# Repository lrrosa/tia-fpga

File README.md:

# tia-fpga

An FPGA replacement for the **Television Interface Adaptor (TIA)** — the custom
`C010444` / `C010444D` (NTSC) video and sound chip of the Atari 2600.

Revision **B** is the digital interface board between a Sipeed Tang Nano 9K
module and the TIA's DIP-40 socket, for use with a real 6507 (on a breadboard or
in an actual 2600). Revision A, the first study, was never built.

| Front | Back |
|:---:|:---:|
|  |  |
| Tang Nano sockets face **up**; the logic sits in the channel between the rows | The TIA's DIP-40 pins face **down** into the socket, over the ground pour |

61.6 × 34.54 mm, two layers. Every row lands on the 2.54 mm grid — the
DIP-40's 15.24 mm and the Tang Nano's 22.86 mm — and the board is a little
shorter than the module it carries, as it has to be: in a real 2600 the TIA,
the 6507 and the RIOT sit millimetres apart.

---

## Why this exists

The TIA has **6,193 transistors** — 1,657 of which are NMOS pull-ups, leaving
about 4,500 of actual logic. It fits in any modern FPGA with room to spare:
synthesising a known implementation yields **311 flip-flops** and roughly 2,200
basic gates.

Size was never the problem. Two other things are:

1. **The analogue boundary.** The chroma generator is an analogue delay line
   trimmed by an external 500 kΩ potentiometer (pin 10, `DEL`). It has no direct
   digital equivalent.
2. **5 volts.** No FPGA with enough capacity is 5 V tolerant. And the TIA
   generates the 6507's Φ0 clock, which requires
   V<sub>IH</sub> = V<sub>cc</sub> − 0.2 V ≈ **4.8 V** — not a TTL level. A 3.3 V
   output will not clock the 6507 reliably, and the failure mode is nasty: it
   works intermittently, or works cold and quits once warm.

This revision solves (2) and leaves (1) for later.

## What is on the board

| Ref | Part | Function |
|-----|------|----------|
| J1, J4 | 1x24 sockets | Sipeed Tang Nano 9K module (GW1NR-LV9QN88PC6/I5): J1 takes its **J6** row, J4 its **J5** |
| J2, J3 | 1x20 SIP strips | Plug into the DIP-40 socket in place of the C010444 |
| D1 | MBR0540 | Feeds the module's 5 V pin from the socket, and blocks its USB from feeding the console |
| **U1** | **74AHCT125** | **Φ0 and RDY buffer, powered from +5 V.** The critical part |
| U2 | 74LVC245A | D0–D7 bidirectional bus. A side = FPGA, B side = TIA |
| U3 | 74LVC541A | A0–A5 and R/W into the FPGA; Φ2 buffered to a spare pad |
| U4 | 74LVC541A | /CS0, /CS3, triggers I4/I5 and the 3.579545 MHz crystal clock |
| U5 | 74LVC1G32 | `/CS0 OR /CS3`: `/OE` for the 245, and the FPGA's chip select |
| U6–U9 | 74LVC2G07 | Open-drain drivers for SYNC, LUM0–2, COL, BLK, AUD0 and AUD1 |

The video and sound pads — SYNC, LUM0–2, COL, BLK, AUD0 and AUD1 — each go
through one channel of U6–U9. On the die every one of them is a pull-down
transistor and nothing more; the buffers make the board's pins the same, open
drain and 5 V tolerant, so the console's own pull-ups set every level. See
*Pads and levels* below.

Pin 10 (`DEL`) is marked no-connect: it is the colour trim pot, which has no
function in a replacement.

Neither of the 245's control lines comes from the FPGA. The A side faces the
FPGA, so `DIR` can be driven straight from the buffered R/W (`DIR`=1, a read,
sends FPGA → TIA), and `/OE` comes from U5. That is deliberate — see the pin
budget below.

## The pin budget, and why it constrains everything

The Tang Nano 9K's headers are 2×24, but **only 29 of those 48 pins are usable
3.3 V GPIO**:

| | Count | |
|---|---|---|
| J5 pins 1–22 | 22 | banks 1/2 at 3.3 V — all usable |
| J6 pins 1, 10, 11, 19–22 | 7 | 3.3 V — usable |
| J6 pins 2–9 | 8 | **BANK3 at 1.8 V — not usable at 3.3 V** |
| J5 23–24, J6 12–17 | 8 | HDMI differential pairs — not GPIO |
| J6 18, 23, 24 | 3 | +5V (fed through D1), GND, +3V3 |

Verified against both revisions of the official Sipeed board schematic (3672 and
3674), which agree exactly. Many of the 29 are shared with onboard peripherals
(SD card, RGB LCD, SPI LCD); they are free to reuse as long as you do not fit
those.

**Rev B uses all 29 with nothing spare.** A fully featured TIA needs about 36.
`BLK` has its pin because the FPGA reads `/CS0 OR /CS3` from U5, which makes it
for the 245 anyway, instead of taking the two selects separately.

**Chroma is fitted.** `F_COL` took the pin that used to carry Φ2, and that trade
is deliberate rather than grudging: the FPGA generates Φ0 itself, so it knows
where it is in the bus cycle and can time accesses off its own clock instead of
the 6507's output. It costs a little timing fidelity and buys back colour on the
composite and RF path — which is the difference between a board that only works
with an HDMI monitor and one that revives a console with a dead TIA while
keeping its original video. Φ2 is still buffered by U3, brought out to an
unconnected pad for a future revision.

What still does not fit: the four paddle inputs plus their dump/compare control.

Two ways to get the remaining pins back:

1. **Recover J6/2–9** (8 pins) with a local 1.8 V LDO and a fourth buffer powered
   at 1.8 V. LVC parts run down to 1.65 V and their inputs stay 5 V tolerant, so
   this works — it just adds a rail. This is the cheapest way to the paddles.
2. **Drop the module and put a bare FPGA on the board.** A part in a TQFP-100
   gives ~78 I/O against the module's 29, which ends the pin shortage outright,
   removes U5, brings Φ2 back and makes the paddles possible — and collapses a
   ~20 mm tall stack into a 1 mm chip, which matters if this has to live inside
   a closed console. It costs fine-pitch soldering and your own configuration
   and power plumbing. See `docs/bare-fpga.md`.

This is the single most important thing to know before ordering parts: the Tang
Nano 9K is big enough in *logic* by a wide margin, and tight in *pins*. Every
compromise in this design traces back to that.

## The board

Rev B is a 2-layer, **61.6 × 34.54 mm** board — shorter than the Tang Nano it
carries. In a real 2600 the TIA, the 6507 and the RIOT sit millimetres apart,
ringed by resistor networks and the cartridge slot, so the board cannot spread
sideways. The two sets of rows face opposite ways:

| y (mm) | Row | Side | Faces |
|---|---|---|---|
| 5.84 | J1 — Tang Nano **J6** | F.Cu | socket, **up** |
| 9.65 | J2 — TIA pins 1–20 | **B.Cu** | pins, **down** into the socket |
| 24.89 | J3 — TIA pins 21–40 | **B.Cu** | pins, **down** |
| 28.70 | J4 — Tang Nano **J5** | F.Cu | socket, **up** |

Both pitches land on the 2.54 mm grid: the DIP-40 rows 15.24 mm apart, the Tang
Nano's 22.86 mm, and the DIP pair centred between the sockets — 3.81 mm of gap
on each side. Which socket takes which module row is not free — see
[Which row is which](#which-row-is-which). SMD logic sits on the front in the
15.24 mm channel between the DIP rows. The open-drain drivers and their
capacitors sit in the top margin, right above the TIA pins they drive, with D1
beside them, and the channel's decoupling in the bottom margin.

| | |
|---|---|
| Size | 61.6 × 34.54 mm, 2 layers |
| Components | 24 — SOIC/SOT-23 logic, 0805 capacitors, one diode, through-hole connectors |
| Routing | 534 segments, 39 vias, 1.48 m of copper |
| Ground | B.Cu pour, 759 mm² in two islands, tied together by track |
| Track / clearance | 0.18 mm / 0.13 mm |
| **DRC** | **0 violations, 0 unconnected pads** |

### Pin assignment is solved, not listed

Which signal sits on which header position is free — any GPIO can carry any
signal — so it is chosen to put each FPGA pin as close as it can be to the pad
its net really reaches: the buffer or gate between it and the TIA socket, not
the socket pin beyond it. Solved as an assignment problem (Hungarian, over the
29 usable positions, Manhattan distance to those pads), the whole set comes to
571 mm. `F_OSC` is held to J6/1, the right PLL's own input, which costs 25.6 mm
of that and keeps the colour clock off the FPGA's general routing.

The sum is what the module's own geometry allows: J5 carries 22 of the 29
signals and sits on the row *away* from the TIA's pins 1–20, so most of the bus
crosses the channel whatever the assignment does. Solving it still beats the
alternative — the same signals laid out by hand come to 685 mm.

Rev A measured the distance to the TIA pin itself, which left out the detour
through the buffers: its data and chip-select lines crossed the board twice.
The buffers stay ordered left to right by the centroid of what they carry,
**U1, U4, U3, U2**, and against rev A the board saves copper while gaining five
parts:

| | rev A | rev B |
|---|---|---|
| Segments | 601 | **534** |
| Vias | 31 | **39** |
| Copper | 1.68 m | **1.48 m** |

`fpga/tia_fpga.cst` carries the result. Do not reshuffle those `IO_LOC` lines
casually — the layout depends on them.

Autorouted with [Freerouting](https://github.com/freerouting/freerouting) 2.2.4:
all 120 nets in about 12 s but three ground connections. Two are closed with a
via dropped on the branch's own track where it passes over the pour, and the
last two capacitors are tied to their neighbours along the free lane that runs
just inside the top edge. The channel leaves only ~1.1 mm between the header pads and the SOIC
pads, so the geometry decides whether it routes at all: it takes 0.13 mm
clearance and 0.18 mm track. The ground pour is added **after** routing —
Freerouting reads a pour as an obstacle and goes effectively single-layer if one
is present.

Files: `tia-fpga.kicad_pcb`, renders in `docs/`, fabrication output in `gerbers/`.

### Ordering a board

The files in `gerbers/` are ready for any PCB house as they are — Gerber X2
plus Excellon drill, with `FABRICATION-NOTES.txt` alongside them; zip them with
the files at the root of the archive. Nothing in it needs more than standard
low-cost capability:

| | |
|---|---|
| Size / layers | 61.6 × 34.54 mm, 2 layers, 1.6 mm FR4 |
| Min track / clearance | 0.18 mm / 0.13 mm |
| Drills | 0.30 mm (vias), 1.00 mm (connectors) |

`docs/bom-production.csv` is the parts list with suggested orderable numbers.
Three assembly points that are easy to get wrong:

- **J2/J3 mount on the BACK, pins facing DOWN**, and want **round machined
  pins** — square header pins damage a DIP socket.
- **U5–U9, C7–C10 and D1 carry their designators on the back silkscreen**,
  right behind each part: the top margin has no room for them on the front.
- **The module goes in component side up, USB-C end to the left** — see below.
- **The back silkscreen carries the licence notice** — `CERN-OHL-S v2`,
  `LRRosa 2026` and `github.com/lrrosa/tia-fpga`, between the two rows of TIA
  pins. The licence asks for it to travel with the board; keep it on a respin.
- **Pin 1 of the TIA is at the half-moon end.** The back carries that half moon,
  keyed like the chip's own package, and the numbers 1, 20, 21 and 40 beside the
  corner pads; the front repeats 1 and 40.

### Which row is which

The Tang Nano's two rows are **22.86 mm** apart (9 × 2.54), from Sipeed's own
dimension drawing, `Tang_Nano_9K_3672_size`. Pin 1 of both rows is at the USB-C
end, 2.55 mm from that edge; the HDMI connector is at the other end and
overhangs this board by about 7.5 mm, with a millimetre of module sticking out
at the USB end as well. Both hang in free air, 20 mm above the console.

Looking down at the module with the USB-C end on the left, **J6 is the upper
row and J5 the lower one**, so J1 takes J6 and J4 takes J5. Three things say so
and agree: the pin numbers silkscreened on the module's underside, the QN88's
own pin order on the top-side photo in Sipeed's datasheet, and third-party
carrier boards for the module. On your own board, look for **63** beside pin 1
of one row and **38** beside pin 1 of the other: 63 is J6/1, which this board
wires to `F_OSC`.

Rev A and the first cut of rev B had both of these wrong — 20.32 mm, and the
rows the other way round. Nothing was ever fabricated from them.

The DIP-40 row spacing (15.24 mm) is fixed by the package and is not a guess.

**The board needs tall pins.** It overhangs the neighbouring 6507 and RIOT, which
sit proud of the 2600's PCB in their own sockets. Standard DIP header pins would
put this board straight into them; a socket extender or long machined pins are
required. Measure the vertical clearance in your console — the Tang Nano's HDMI
connector adds roughly 5 mm on top.

**There are no mounting holes.** The board is held by its own pins in the TIA
socket, and there is nothing to screw into inside a 2600. Adding holes only
forced the board larger, so they were dropped.

### Known limitations

- The four paddle inputs still do not fit — see the pin budget above.
- No ground pour on F.Cu; only B.Cu is poured.

### Pads and levels

Reading the die's netlist for the RTL settled something the schematic had
assumed. **Every video and sound pad on the TIA — SYNC, LUM0–2, COL, AUD0,
AUD1, and BLK and RDY too — is a pull-down transistor and nothing else.** None
of them can drive high. Φ0 is the only output with a real driver on both
sides.

The console schematics show the other half:

| | 2600A, rev 16 | 2600 (the original board) |
|---|---|---|
| LUM0–2, SYNC | R218–R221, 3.3–4.7 kΩ to +5 V, straight into the summing resistors (R214–R217: 27, 47, 110, 24 kΩ) | R218–R221, 3.3 kΩ to +5 V, into a CD4050 run from a divider off +5 V (R231, R232: about 3.6 V), then the summing resistors (R222–R224, R234: 12, 24, 47, 10 kΩ) |
| COL | R228, 1 kΩ to +5 V; C210, 47 pF, to a second 1 kΩ pull-up (R211); 6.8 kΩ and 22 pF into the sum | R212, 1 kΩ to +5 V; C212, 47 pF, to a second 1 kΩ pull-up (R214); 22 pF and 6.8 kΩ into the sum |
| BLK | R234, 820 Ω, into the COL node (revs 14 and 15: not connected) | R213, 680 Ω, into the COL node |
| AUD0, AUD1 | joined; R206, 1 kΩ to +5 V; 0.1 µF and 18 kΩ into the sound oscillator | joined; R208, 1 kΩ to +5 V; the same coupling |

PAL consoles use a different TIA (C011903): one sound pad, AUD on pin 13 with
its own 1 kΩ pull-up, while pins 12 and 8 carry the PAL signals. This board is
for the NTSC chip.

Rev B follows the die:

- **Open drain, 5 V tolerant.** Each of those pads goes through one channel of
  a 74LVC2G07 (U6–U9) powered at 3.3 V. The FPGA drives the channel's input:
  0 pulls the socket pin low, 1 lets it go, and the console's pull-up takes the
  line wherever it took the TIA's — 5 V on a 2600A's luma lines, the CD4050's
  input on an original 2600, the colour and sound nodes through their 1 kΩ.
  Nothing on the socket side reaches the FPGA's pins.
- **BLK is driven.** It pulls low through the whole blanking interval. On the
  original 2600 (through 680 Ω) and the 2600A from rev 16 (820 Ω) it drags the
  colour node down with it: against the 1 kΩ pull-up that node only reaches
  about 2 V while blanking, so the burst — the only colour sent then — gets
  well under half the swing of the picture's colour, and a TV sets its colour
  gain by the burst. On revs 14 and 15 of the 2600A the pin is not connected,
  and nothing changes.
- **The two sound pins are joined** by a trace on an unmodified 2600, which
  open drain makes harmless either way. By default `tia_board.v` still puts
  the same pulse-width mix of both channels on both pins; for a console
  modified for stereo, `AUDIO_STEREO = 1` gives each pin its own channel, in
  non-overlapping halves of the pulse frame so the two still add correctly
  wherever they meet.
- **No video network on the board.** Rev A carried a copy of the console's
  resistor network, for use outside a console. With open-drain pads it would
  have needed all of it — pull-ups, summing resistors, the colour coupling and
  BLK's resistor — so rev B leaves it off. To take video from the socket pins
  on a breadboard, build the 2600A rev 16 column of the table above.

## Two ways to use this

**Reviving a dead console.** Pull the failed TIA, drop this in its socket, and
keep the 2600's own RF modulator or composite mod. Chroma, luma, sync and audio
come out on the same socket pins the original chip used, open drain as the
chip's are, so the console's video path is untouched.

**As a development target.** Plug it into a breadboard next to a real 6507.
The Tang Nano's HDMI connector would cost no header pins — its pins are
dedicated differential pairs on the module — but the RTL has no TMDS encoder
yet, so for now the picture comes from the socket pins, through a network like
the console's.

## The RTL

`rtl/` holds the core: horizontal counter, playfield, two players, two
missiles, ball, collisions, HMOVE, audio and the bus interface, in eleven files
of plain Verilog-2005, plus `tia_board.v`, which puts it on this board. `sim/`
holds the test harness the section below argues for, and it is not
aspirational: the core is checked against
[Sim2600](https://github.com/gregjames/Sim2600) half clock by half clock, on a
real game and on test cartridges written to hit each feature from every phase
that matters.

```bash
python sim/run.py
```

Against Donkey Kong from power-on to its first picture, and against every test
cartridge -- playfield, players, missiles, ball, collisions, HMOVE with Cosmic
Ark, resets at every phase of HBLANK, vertical delay and both sound cartridges
-- the core matches the die on every pin at every half clock.
[`sim/README.md`](sim/README.md) has the table. (The Donkey Kong traces are regenerated locally rather
than committed, since they carry the game's artwork.)

**Sim2600 wires one clock wrong, and both wirings are now in the suite.**
Upstream Sim2600 feeds the TIA's Φ2 input from the 6507's Φ1 output, the
inverse of what the console does. The die only looks at that pin through
write strobes, so everything still worked, but every write landed on the other
half of the colour clock from where a real console puts it. With the console's
wiring (`sim/patches/sim2600-phi2.patch`, traces in `sim/traces/phi2/`), five
of the core's timing rules turned out to have been fitted to the wrong side
and were re-read from the netlist — RSYNC's restart, RDY's release, how
long a reset holds an object's clock, the size gate of stretched players and
when HMOVE's comparators see a new value. The last mismatch was a mechanism
no rule had covered: HMOVE pulses in the visible line merge into the object
clocks and show on the pads half a colour clock early. The core now matches
both sets on every pin of every trace.

**The board.** `rtl/tia_board.v` is everything between the core and the board's
pins: the core's clock from a PLL locked to the console's crystal, Φ2 rebuilt
from the Φ0 the board makes itself, the data bus, chroma as that clock shifted
in phase by hue, and sound as pulse width. `fpga/tia_fpga_top.v` adds the Gowin
PLL, bus buffers and chroma ODDR. `sim/tb_board.v` replays the console-wired
traces into the board logic and checks every pin it drives, and
`fpga/build_gowin.tcl` builds the bitstream with Gowin EDA — from a directory
whose path has no spaces, since Gowin's place and route will not run in one
that does.

Getting there turned up a good deal the published documentation does not say,
all of it now in the source: which edge of the colour clock each latch runs on;
that Φ0 is a 50 per cent square wave reloaded by the horizontal counter; what
RSYNC actually does, which Towers left as "requires more investigation"; that
HMOVE's first compare must come before its first decrement, or an HMxx of -8
moves an object sixteen pixels the wrong way; that HMOVE's pulses past HBLANK
merge into the object clocks instead of counting; and exactly when a mid-line playfield
write reaches the screen. Once the harness could record the die's internal
wires as well as its pins, the netlist itself settled the rest: how a RESxx
strobe really resets an object -- by holding its clock, not by zeroing its
counter -- and how the sound counters are clocked, down to the discovery that
the two audio channels are not wired alike.

**Clocking.** The real chip is clocked by the 3.58 MHz colour clock and uses
both its edges. This core takes a faster system clock and treats the colour
clock as a signal to oversample, so everything is one clock domain, one edge,
no gated clocks. On this board `clk0` comes from the console's own crystal
through U4 and the system clock from a PLL, so the core stays locked to the
machine it is plugged into.

## Status

- [x] Rev B schematic — passes KiCad 10 ERC with 0 violations
- [x] FPGA pin assignment (`fpga/tia_fpga.cst`)
- [x] PCB layout — rev B routed, ground pour, DRC clean (0 violations, 0
      unconnected pads)
- [x] Open-drain video and sound pads and `BLK` on pin 6 — U6–U9, with
      `sim/tb_board.v` checking `BLK` against the die
- [x] Sim2600 test harness — traces, replay testbench, test cartridges
- [x] TIA RTL — matches the die on a real game and on every test cartridge
- [x] Audio -- read off the die's netlist; both channels match on every trace
- [x] Object resets, scan clock, widths and HMOVE timing -- read off the netlist
- [x] Board wrapper — `rtl/tia_board.v` and `fpga/tia_fpga_top.v`: PLL off the
      console's crystal, Φ2 rebuilt from Φ0, data bus tri-state, chroma through
      an ODDR, sound as pulse width. Checked pin by pin against the traces by
      `sim/tb_board.v`
- [x] Traces with the console's wiring of Φ2 — Sim2600 feeds the TIA the
      6507's Φ1; `sim/patches/sim2600-phi2.patch` fixes that and
      `sim/traces/phi2/` holds the re-recorded set
- [x] Synthesis check: Yosys `synth_gowin` with no warnings — the core is
      514 flip-flops and 740 LUTs, the whole board top 622 and 705, under
      10 per cent of the GW1NR-9 (`fpga/check_synth.py`)
- [x] Gowin EDA build (V1.9.11.03 Education): bitstream, no setup or hold
      violations at the slow corner, 60.4 MHz Fmax against the 57.27 MHz
      clock (`fpga/build_gowin.tcl`)
- [x] Stretched players reset mid-copy, Cosmic Ark and HMOVE pulses in the
      visible line, with the console's wiring — every trace matches
- [ ] Paddle circuit (still needs pins, see above)
- [x] Composite video path wired — the chroma pin is fitted and `tia_board.v`
      synthesises the 15 subcarrier phases, as the colour clock shifted in
      phase by hue through an ODDR (`HUE_TURN`). Never yet seen on a television
- [x] Tang Nano interface checked against Sipeed's own dimension drawing: rows
      22.86 mm apart, J6 on J1, and the module fed from the socket through D1
- [x] Boot time — the bitstream loads at 31.25 MHz (`-loading_rate 250/8` in
      `fpga/build_gowin.tcl`), about 8 ms, against the 17–58 ms the console
      takes to release the 6507's reset. Still to be measured on hardware

## Opening the project

Requires **KiCad 10**. Only stock libraries are used — there are no custom
symbols or footprints to install.

```bash
kicad tia-fpga.kicad_pro
```

To run ERC from the command line:

```bash
kicad-cli sch erc tia-fpga.kicad_sch -o erc.rpt --severity-error --severity-warning
```

## Suggested order of work

1. ~~**Build the test harness first.**~~ Done -- `sim/`. Comparing half clock
   by half clock against [Sim2600](https://github.com/gregjames/Sim2600) -- not
   an emulator, but the netlist extracted from the die shot, simulated
   transistor by transistor -- earned its keep at once. Most of what it caught
   were things the documentation states plainly enough that they looked
   settled, and none of them would have been findable by looking at a picture.
2. ~~**Rewrite the TIA one block at a time**~~ -- done, in dependency order:
   horizontal sync counter, playfield, players, missiles and ball, collisions,
   HMOVE. HMOVE really is the most treacherous; leave it last.
3. ~~**Widen the coverage.**~~ Done: the test cartridges in `sim/roms/` cover
   every CTRLPF, NUSIZ, HMOVE and AUDC value, and resets at every phase of
   HBLANK, and the core matches the die on all of them.
4. ~~**Board wrapper and synthesis**~~ -- done: `rtl/tia_board.v`,
   `fpga/tia_fpga_top.v`, `fpga/tia_fpga.sdc`, `fpga/build_gowin.tcl`.
5. **Run it on the Tang Nano alone** before touching real hardware, to separate
   bugs in the TIA from bugs in your bench wiring. Nothing here does that yet:
   the module would need the rest of the console beside the core -- a 6502, the
   RIOT and a cartridge image -- or a player that replays the recorded bus
   writes in `sim/traces/`, and either way a TMDS encoder and line doubling to
   put the picture on HDMI.
6. **This board** -- TIA-only, with a real 6507.
7. Paddles.
8. Composite colour: the phases are generated; what is left is a television to
   check the hues and the burst level against.

## Timing quirks that matter

Almost every one of these is a bug in the original chip that games came to rely
on. They are what separates "runs Combat" from "runs Pitfall II":

- **Almost none of the TIA's counters are binary.** They are polynomial
  counters (LFSRs) with wired-AND decode matrices — the horizontal sync
  counter, all five object position counters, and the audio generators. Binary
  counters with comparators will run games but get the edge effects wrong. The
  exception is each sound channel's frequency divider: a binary counter
  *compared* with AUDF, not loaded from it, so lowering AUDF below the count
  makes it run on to 31 before the channel ticks again.
- **HMOVE comb.** Strobing `HMOVE` delays the end of HBlank (the LRHB line),
  producing the 8-pixel black bar at the left edge. Pitfall II depends on it.
- **Cosmic Ark starfield.** Writing HMxx during the HMOVE window makes the
  comparator see a still-running counter. The resulting pattern *differs between
  TIA revisions*.
- **RESPn latency.** A reset strobe does not zero the counter. It holds the
  object's two-phase clock in H@1 and sets a latch, and the counter clears on
  the next H@2. A copy that was already decoded therefore survives the reset,
  and inside HBlank, where the object clock is stopped, the clear waits for
  the first colour clocks of the visible line.
- There are at least **12 NTSC TIA revisions** with observable differences.
  Decide which one you are cloning before you start.

## References

- [TIA Hardware Notes](https://www.atarihq.com/danb/files/TIA_HW_Notes.txt) — Andrew Towers, 2003. Polynomial counters, HCount tables, HMOVE timing. Does not cover audio or colour generation.
- [TIA internal schematics](https://www.atariage.com/2600/archives/schematics_tia/index.html) — 5 sheets scanned by Mark De Smet. Sheet 1: sync counter, playfield and motion registers. Sheet 2: collision register. Sheet 3: object/missile motion counters. Sheet 4: audio circuits. Sheet 5: ball motion counter.
- [10444D die shots](http://www.visual6502.org/images/pages/Atari_10444D_TIA.html) — visual6502
- [TIA Technical Manual](https://archive.org/stream/Atari_2600_TIA_Technical_Manual/Atari_2600_TIA_Technical_Manual_djvu.txt)
- [Atari 2600 Specs](https://problemkaputt.de/2k6specs.htm) — Nocash; the cleanest register map there is
- [Tang Nano 9K documentation](https://dl.sipeed.com/shareURL/TANG/Nano%209K/) — Sipeed

---

## Licence

Copyright 2026 Leonardo Roman da Rosa

```
SPDX-License-Identifier: CERN-OHL-S-2.0
```

This source describes Open Hardware and is licensed under the CERN-OHL-S v2.

You may redistribute and modify this source and make products using it under
the terms of the CERN-OHL-S v2 (https://ohwr.org/cern_ohl_s_v2.txt).

This source is distributed WITHOUT ANY EXPRESS OR IMPLIED WARRANTY, INCLUDING OF
MERCHANTABILITY, SATISFACTORY QUALITY AND FITNESS FOR A PARTICULAR PURPOSE.
Please see the CERN-OHL-S v2 for applicable conditions.

Source location: https://github.com/lrrosa/tia-fpga

As per CERN-OHL-S v2 section 4, should You produce hardware based on this source,
You must where practicable maintain the Source Location visible on the external
case of the Gizmo or other products you make using this source.

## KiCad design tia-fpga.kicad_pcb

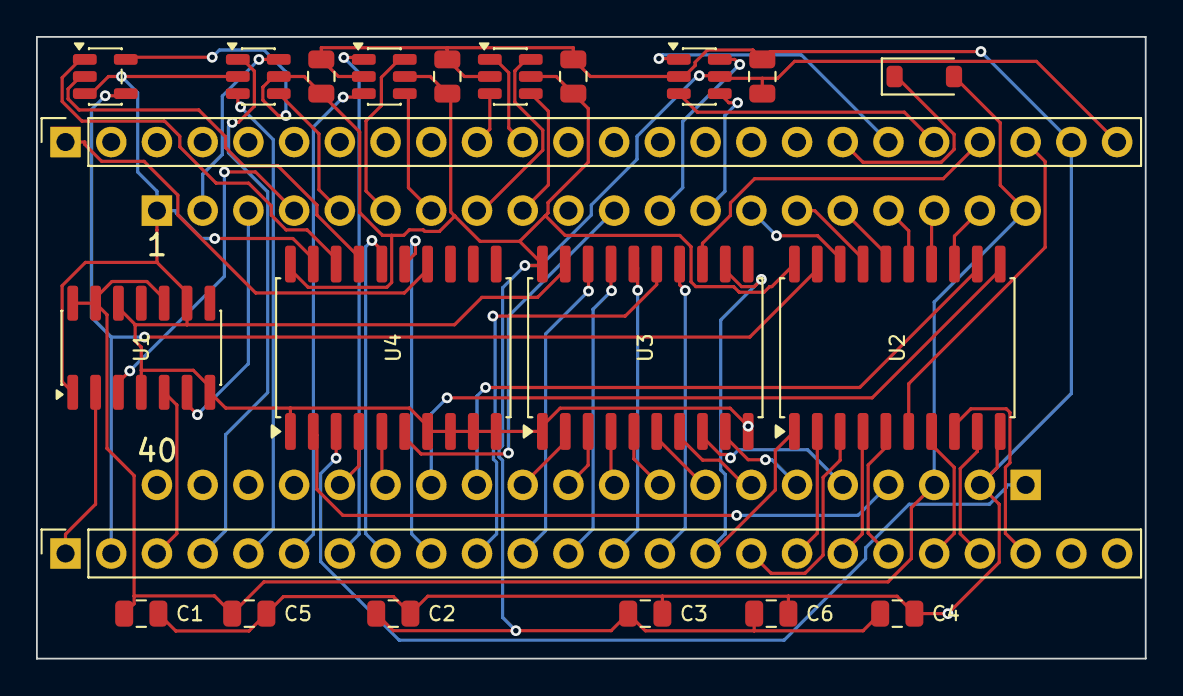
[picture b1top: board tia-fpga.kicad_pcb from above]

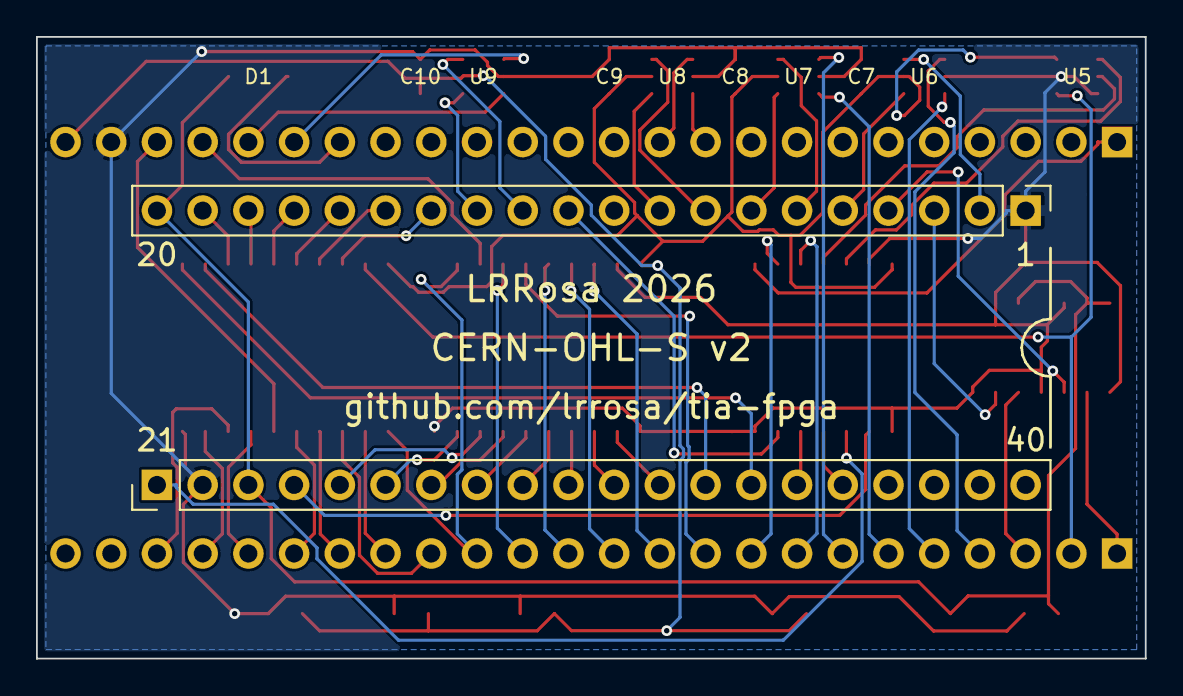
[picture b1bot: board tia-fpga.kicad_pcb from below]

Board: 2 copper layers, 61.6 x 34.5 mm, 24 parts (2 on the bottom side), 66 nets.

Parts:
C1, C2, C3, C4, C5, C6: C_0805_2012Metric
C7, C8, C9, C10: 100n; C_0805_2012Metric
D1: MBR0540; D_SOD-123
J1, J4: PinSocket_1x24_P2.54mm_Vertical
J2, J3: PinHeader_1x20_P2.54mm_Vertical
U1: SOIC-14_3.9x8.7mm_P1.27mm
U2, U3, U4: SOIC-20W_7.5x12.8mm_P1.27mm
U5: SOT-23-5
U6, U7, U8, U9: 74LVC2G07; SOT-23-6

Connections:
+3V3: C2.1, C3.1, C4.1, C6.1, C7.1, C8.1, C9.1, C10.1, J1.24, U2.20, U3.20, U4.20, U5.5, U6.5, U7.5, U8.5, U9.5
+5V: C1.1, C5.1, D1.2, J2.20, J3.3, U1.10, U1.13, U1.14
/F_A0: J4.11, U3.18
/F_A1: J4.12, U3.17
/F_A2: J4.13, U3.16
/F_A3: J4.10, U3.15
/F_A4: J4.14, U3.14
/F_A5: J1.21, U3.13
/F_AU0: J1.20, U9.3
/F_AU1: J1.19, U9.1
/F_BLK: J4.7, U7.1
/F_COL: J1.10, U8.3
/F_CS0_N: U4.18, U5.1
/F_CS3_N: U4.17, U5.2
/F_CSYNC: J4.4, U6.1
/F_CS_N: J4.2, U2.19, U5.4
/F_D0: J4.17, U2.2
/F_D1: J4.16, U2.3
/F_D2: J4.18, U2.4
/F_D3: J4.19, U2.5
/F_D4: J1.22, U2.6
/F_D5: J4.20, U2.7
/F_D6: J4.22, U2.8
/F_D7: J4.21, U2.9
/F_I4: J4.8, U4.16
/F_I5: J4.9, U4.15
/F_LUM0: J1.11, U8.1
/F_LUM1: J4.5, U6.3
/F_LUM2: J4.6, U7.3
/F_OSC: J1.1, U4.14
/F_PHI0: J4.1, U1.2
/F_RDY: J4.3, U1.5
/F_RW: J4.15, U2.1, U3.12
/TIA_A0: J3.12, U3.2
/TIA_A1: J3.11, U3.3
/TIA_A2: J3.10, U3.4
/TIA_A3: J3.9, U3.5
/TIA_A4: J3.8, U3.6
/TIA_A5: J3.7, U3.7
/TIA_AU0: J2.13, U9.4
/TIA_AU1: J2.12, U9.6
/TIA_BLK: J2.6, U7.6
/TIA_COL: J2.9, U8.4
/TIA_CS0_N: J3.4, U4.2
/TIA_CS3_N: J3.1, U4.3
/TIA_CSYNC: J2.2, U6.6
/TIA_D0: J2.14, U2.18
/TIA_D1: J2.15, U2.17
/TIA_D2: J2.16, U2.16
/TIA_D3: J2.17, U2.15
/TIA_D4: J2.18, U2.14
/TIA_D5: J2.19, U2.13
/TIA_D6: J3.13, U2.12
/TIA_D7: J3.14, U2.11
/TIA_I4: J3.16, U4.4
/TIA_I5: J3.15, U4.5
/TIA_LUM0: J2.8, U8.6
/TIA_LUM1: J2.5, U6.4
/TIA_LUM2: J2.7, U7.4
/TIA_OSC: J2.11, U4.6
/TIA_PHI0: J2.4, U1.3
/TIA_PHI2: J3.6, U3.9
/TIA_RDY: J2.3, U1.6
/TIA_RW: J3.5, U3.8
/TN_5V: D1.1, J1.18
GND: C1.2, C2.2, C3.2, C4.2, C5.2, C6.2, C7.2, C8.2, C9.2, C10.2, J1.23, J2.1, J3.2, U1.1, U1.4, U1.7, U1.9, U1.12, U2.10, U3.1, U3.10, U3.19, U4.1, U4.7, U4.8, U4.9, U4.10, U4.19, U5.3, U6.2, U7.2, U8.2, U9.2

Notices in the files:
tia-fpga.kicad_pcb:
Leonardo Roman da Rosa - CERN-OHL-S-2.0
